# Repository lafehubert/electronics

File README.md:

# electronics
A place for info and code relating to my electronics projects

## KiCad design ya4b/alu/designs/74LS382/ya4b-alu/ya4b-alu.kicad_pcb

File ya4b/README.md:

Here be schematics and PCB designs for YA4B, the 4-bit computer I'm designing.

I use KiCad (https://www.kicad-pcb.org/) for the designs, and an Arduino Mega 2560 to run the test code.

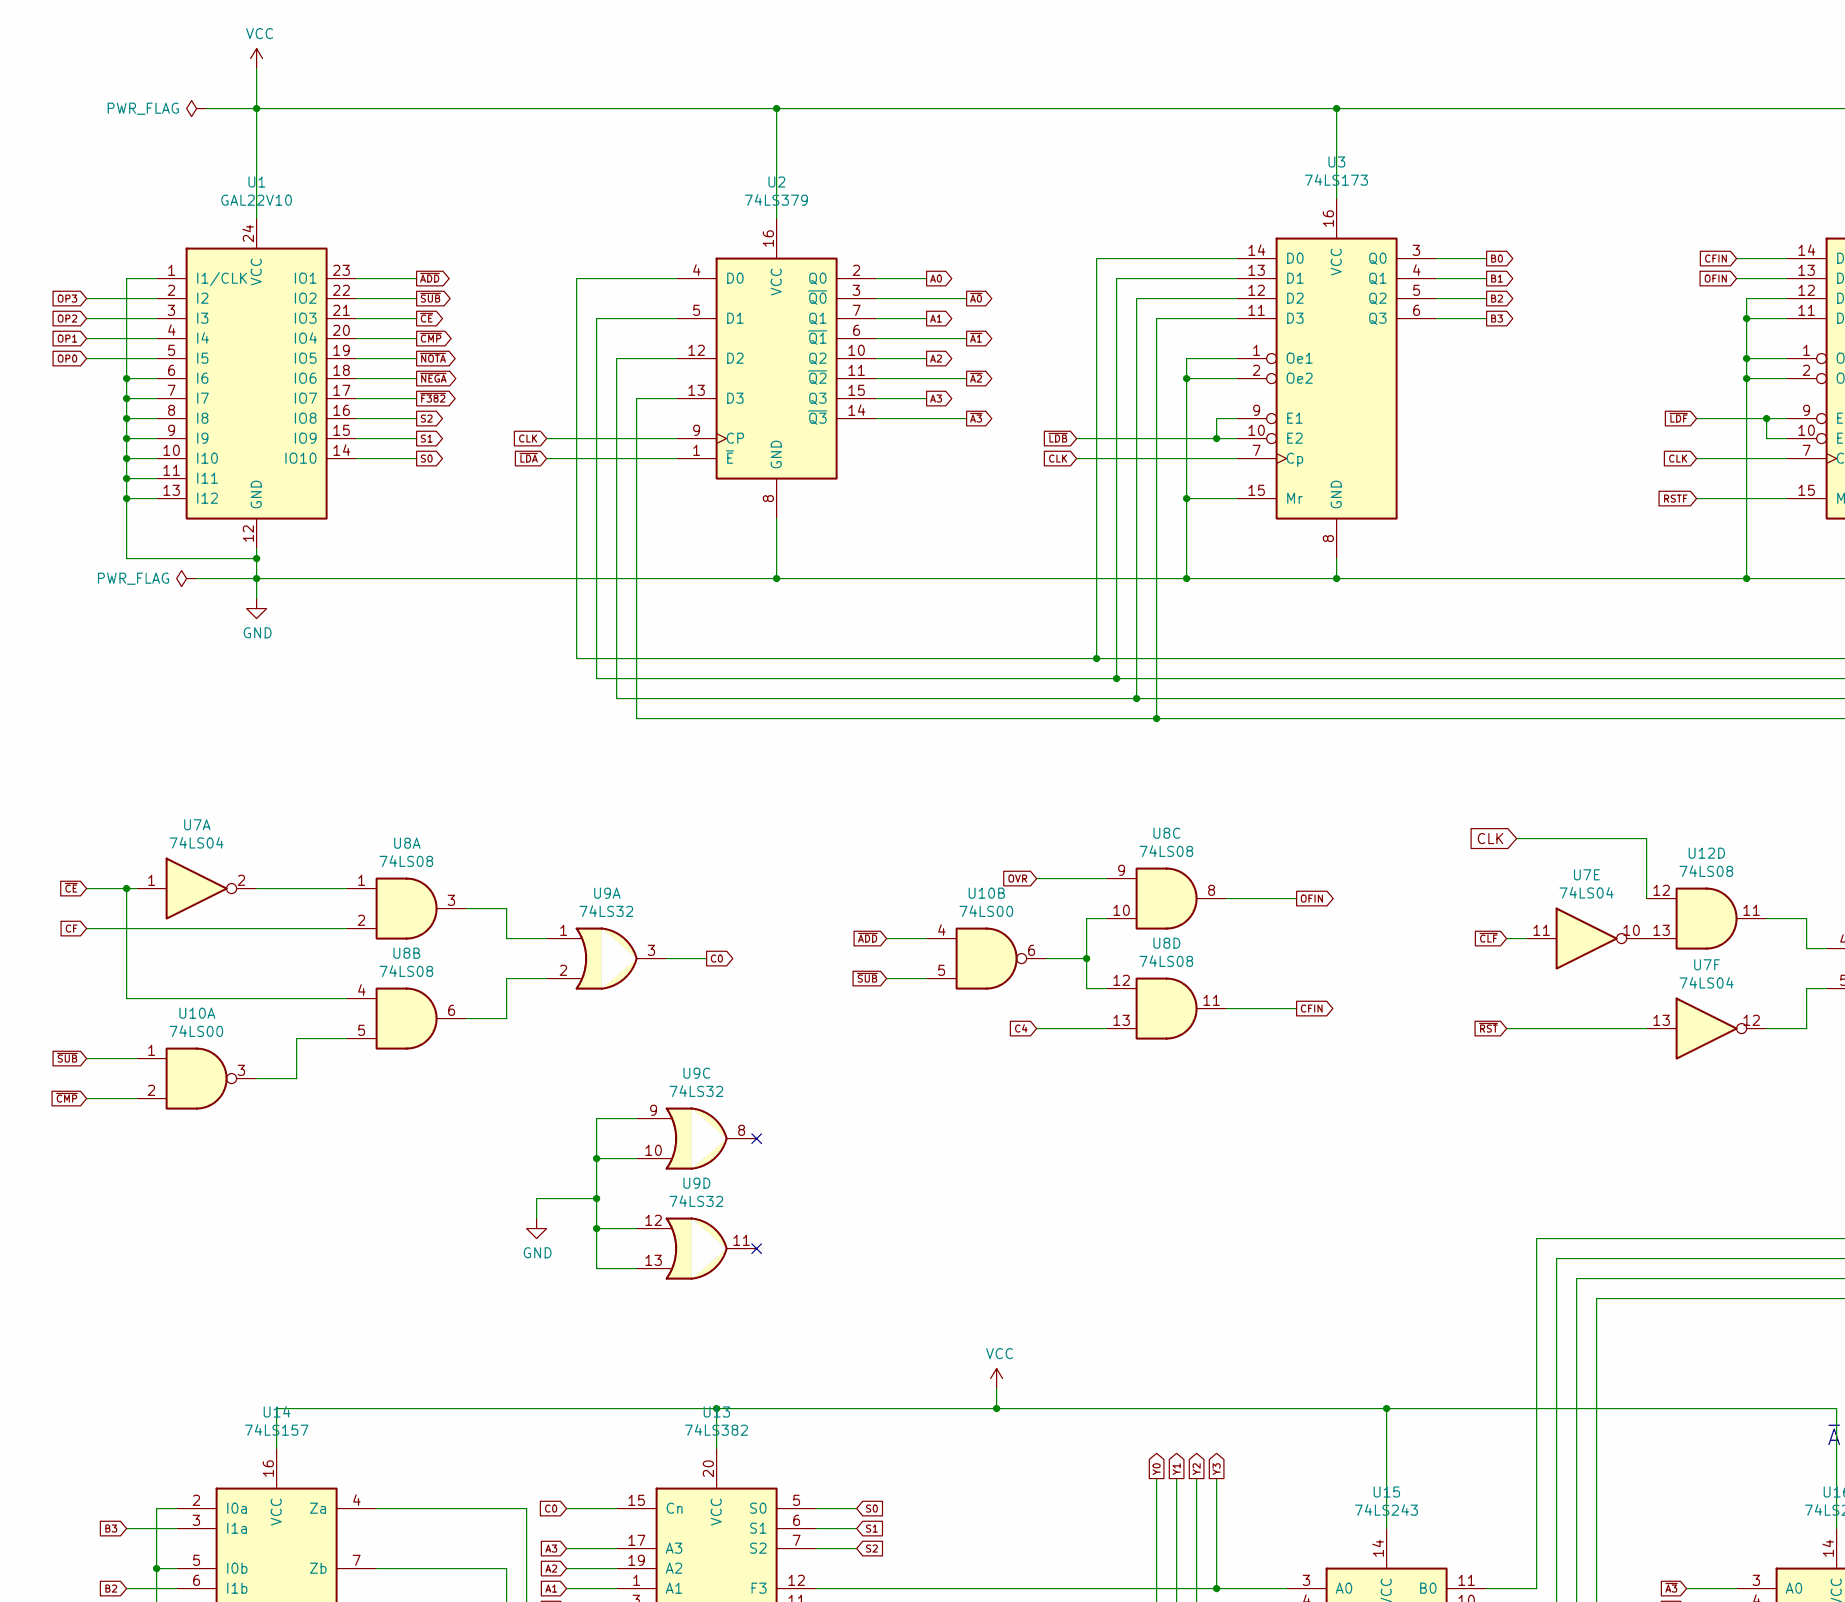
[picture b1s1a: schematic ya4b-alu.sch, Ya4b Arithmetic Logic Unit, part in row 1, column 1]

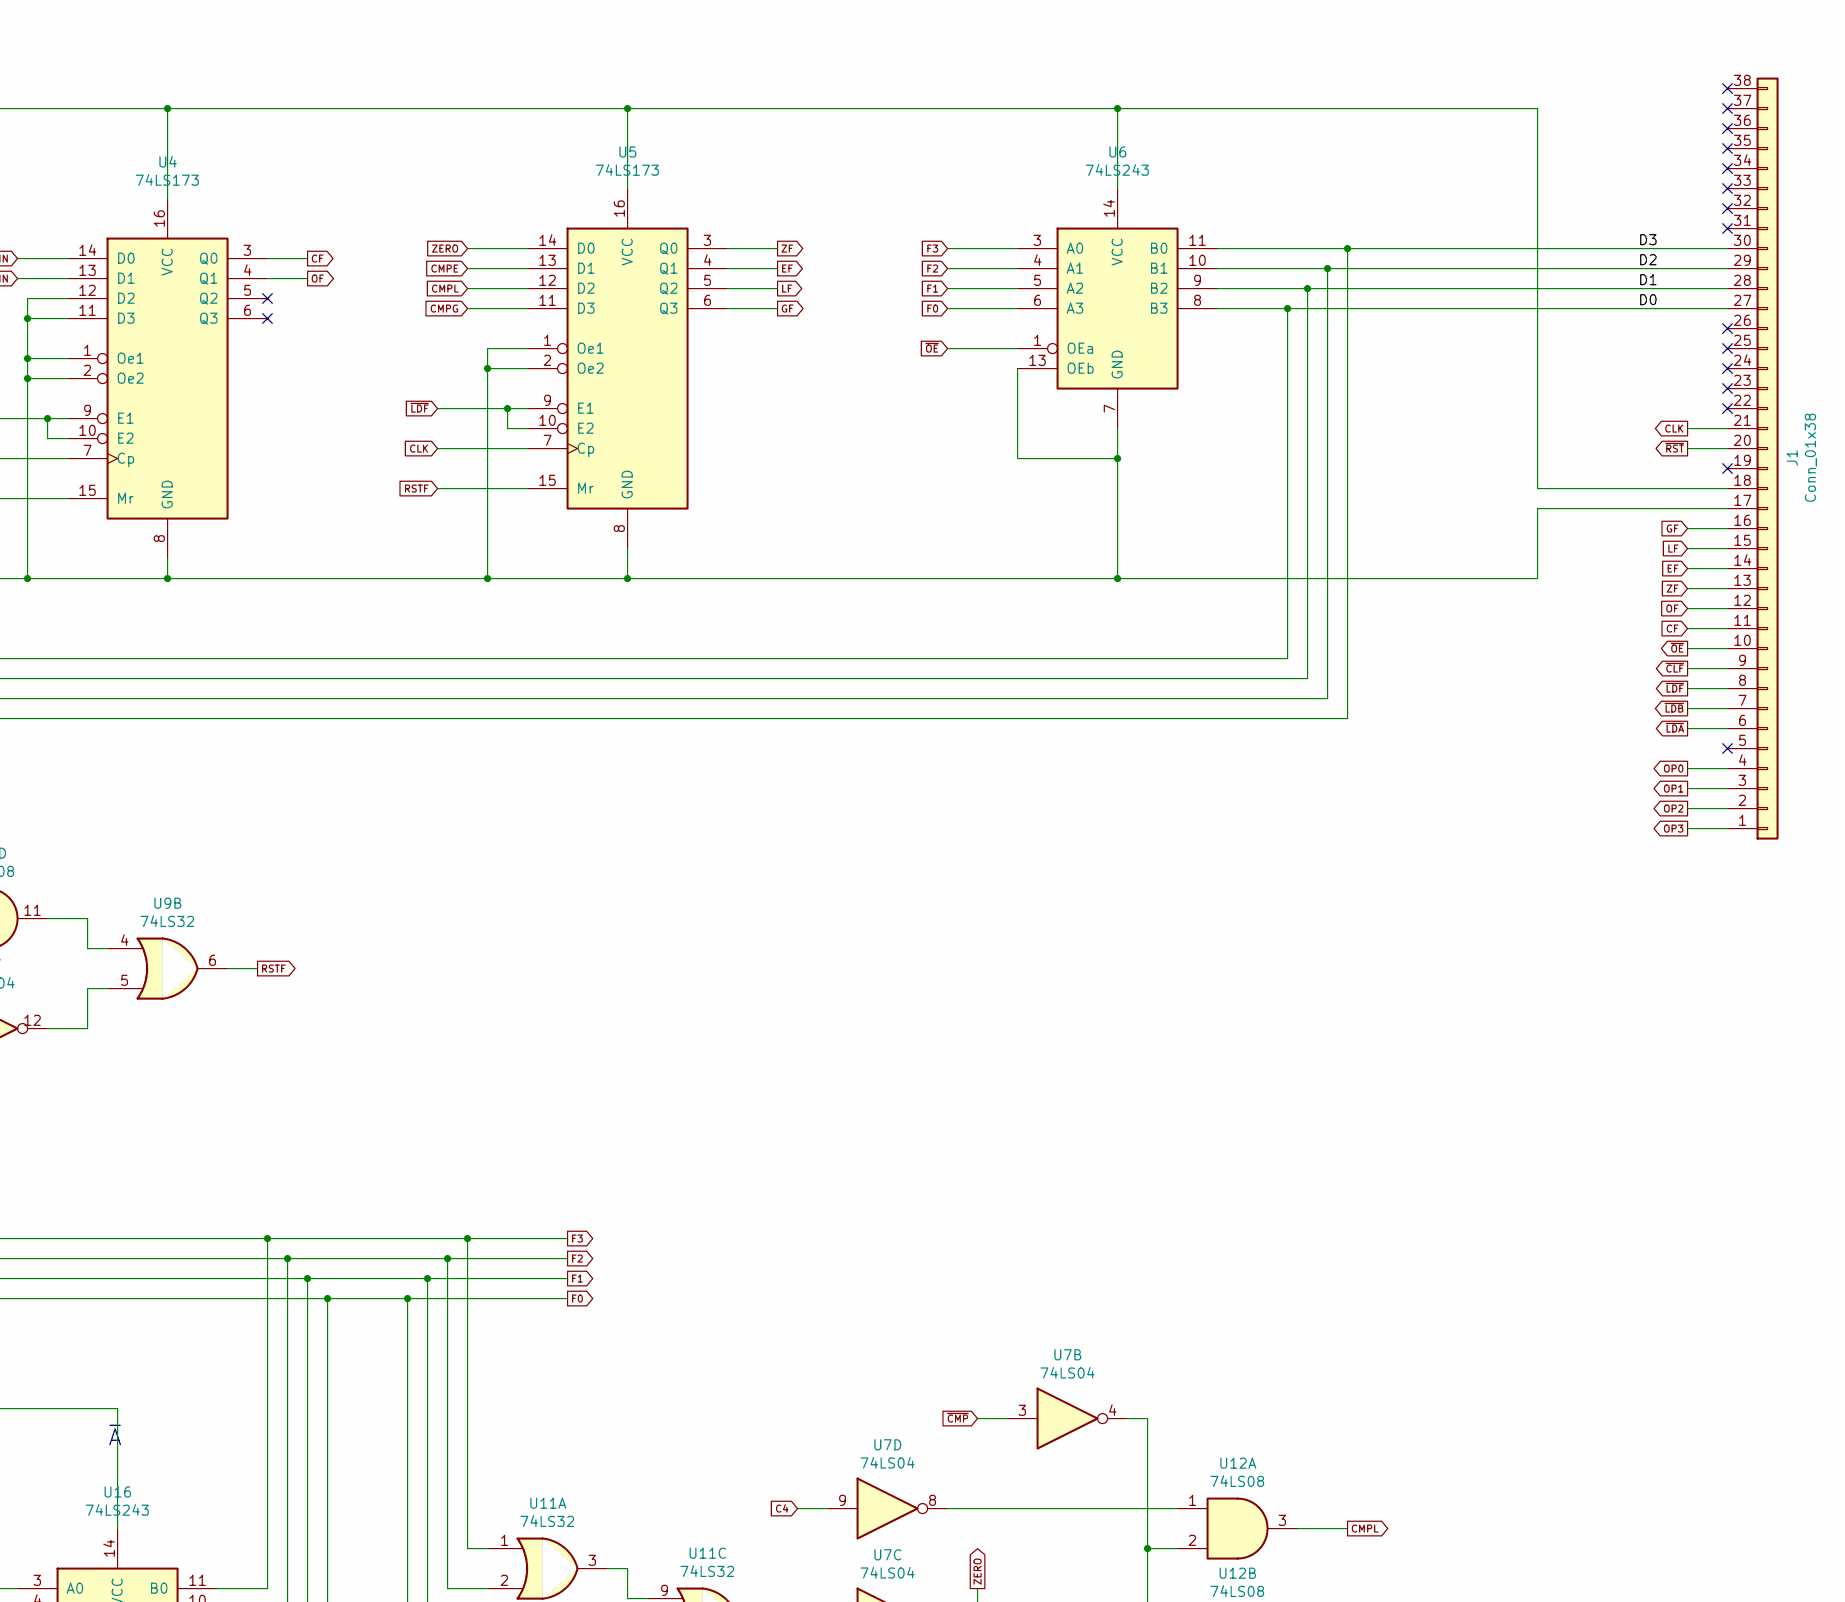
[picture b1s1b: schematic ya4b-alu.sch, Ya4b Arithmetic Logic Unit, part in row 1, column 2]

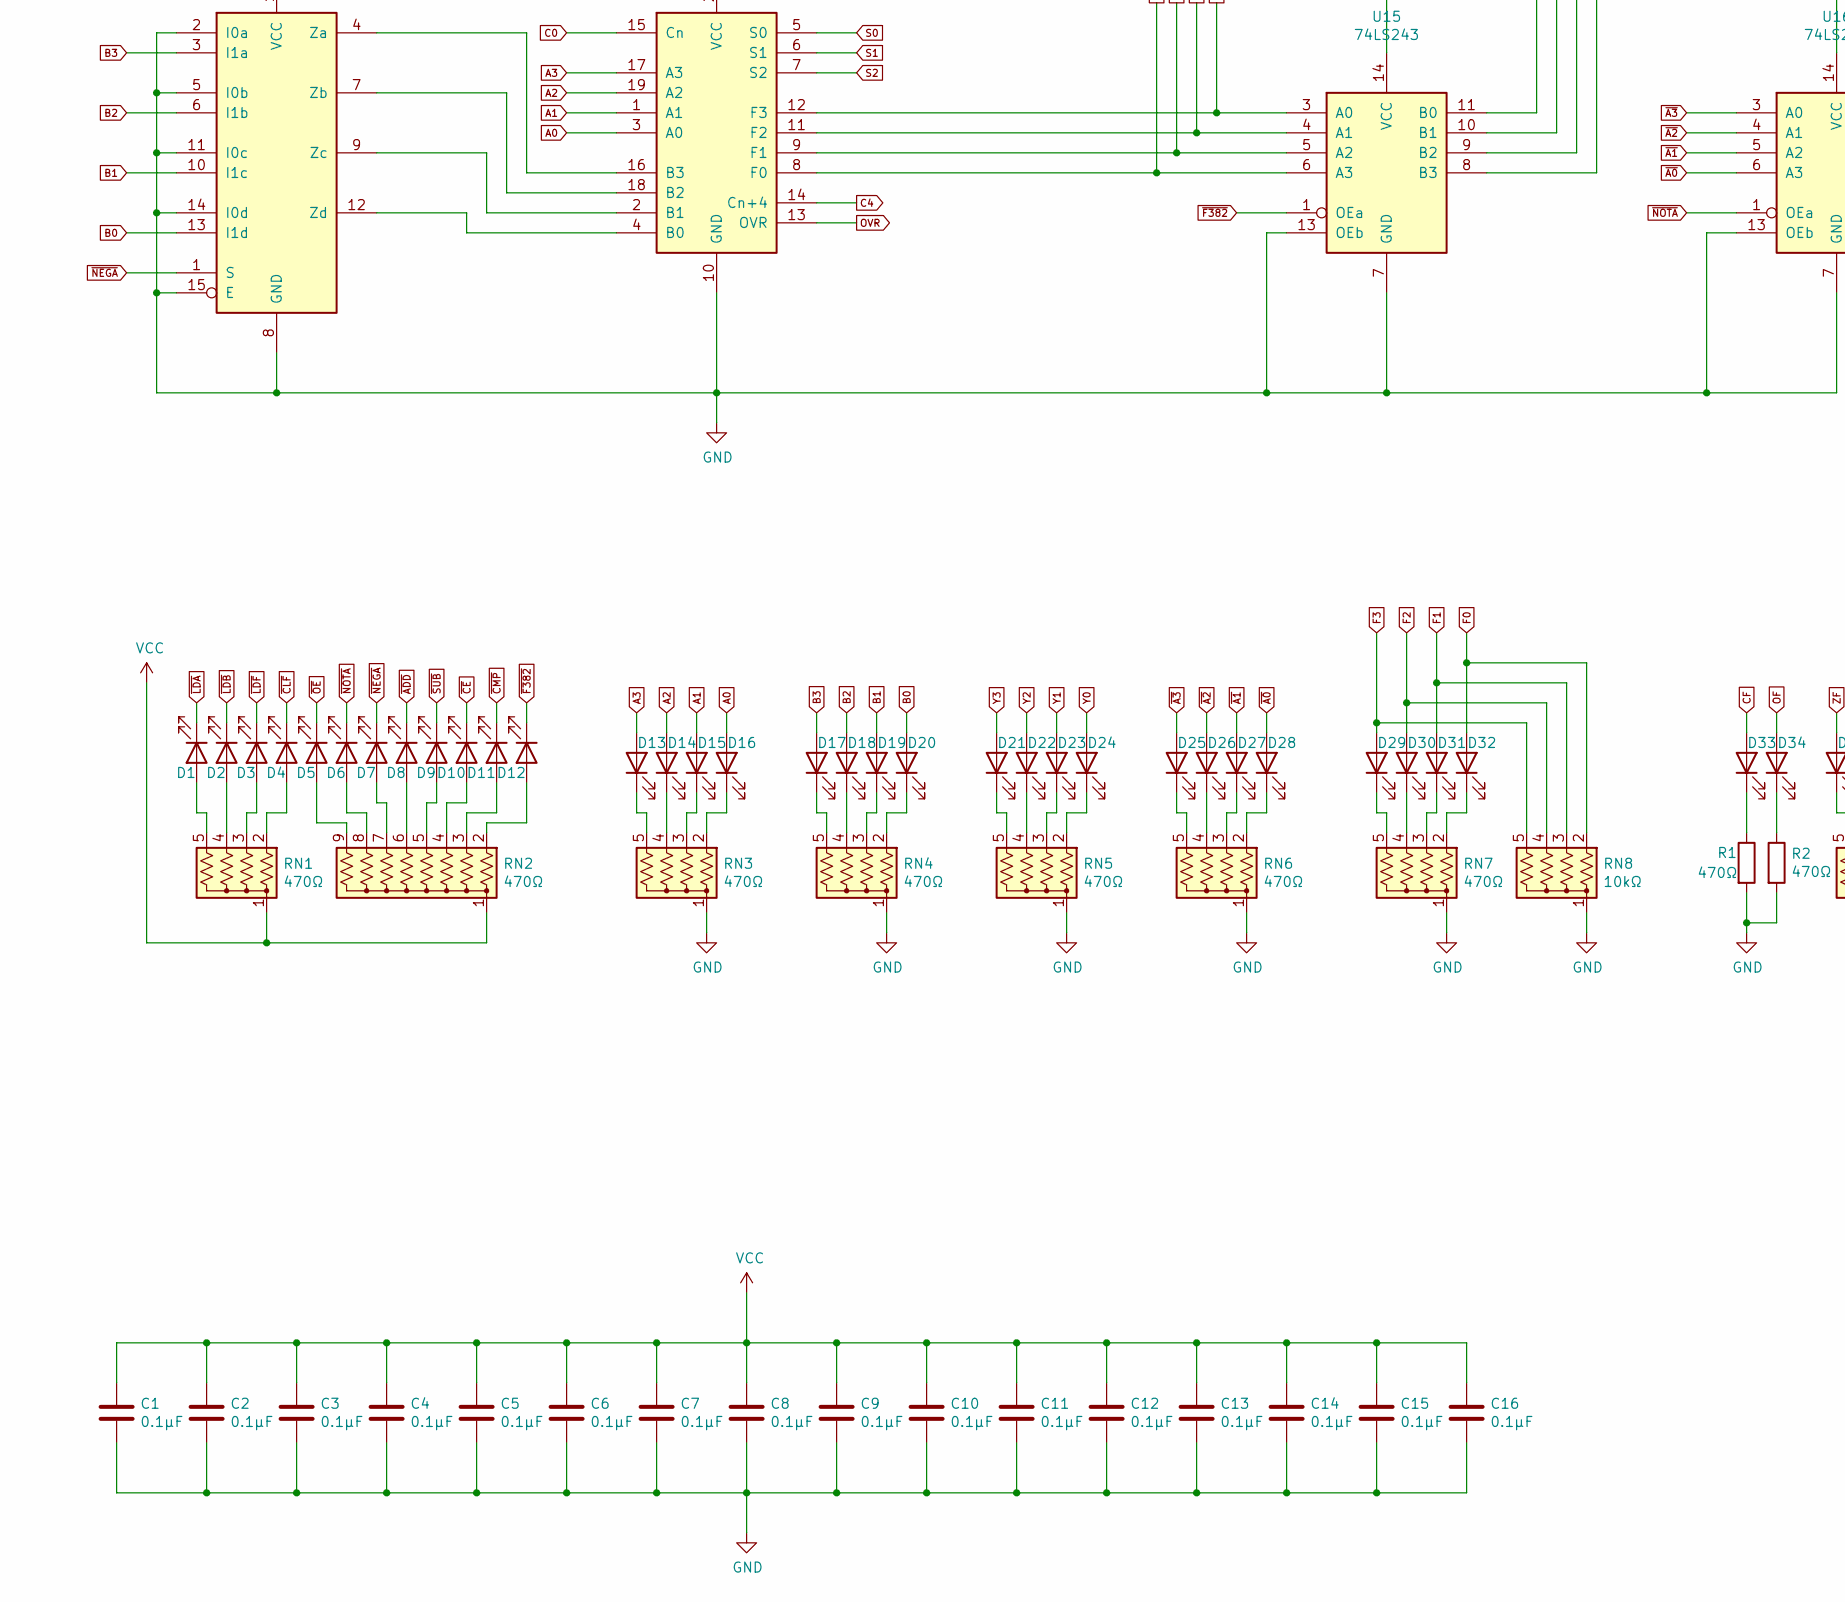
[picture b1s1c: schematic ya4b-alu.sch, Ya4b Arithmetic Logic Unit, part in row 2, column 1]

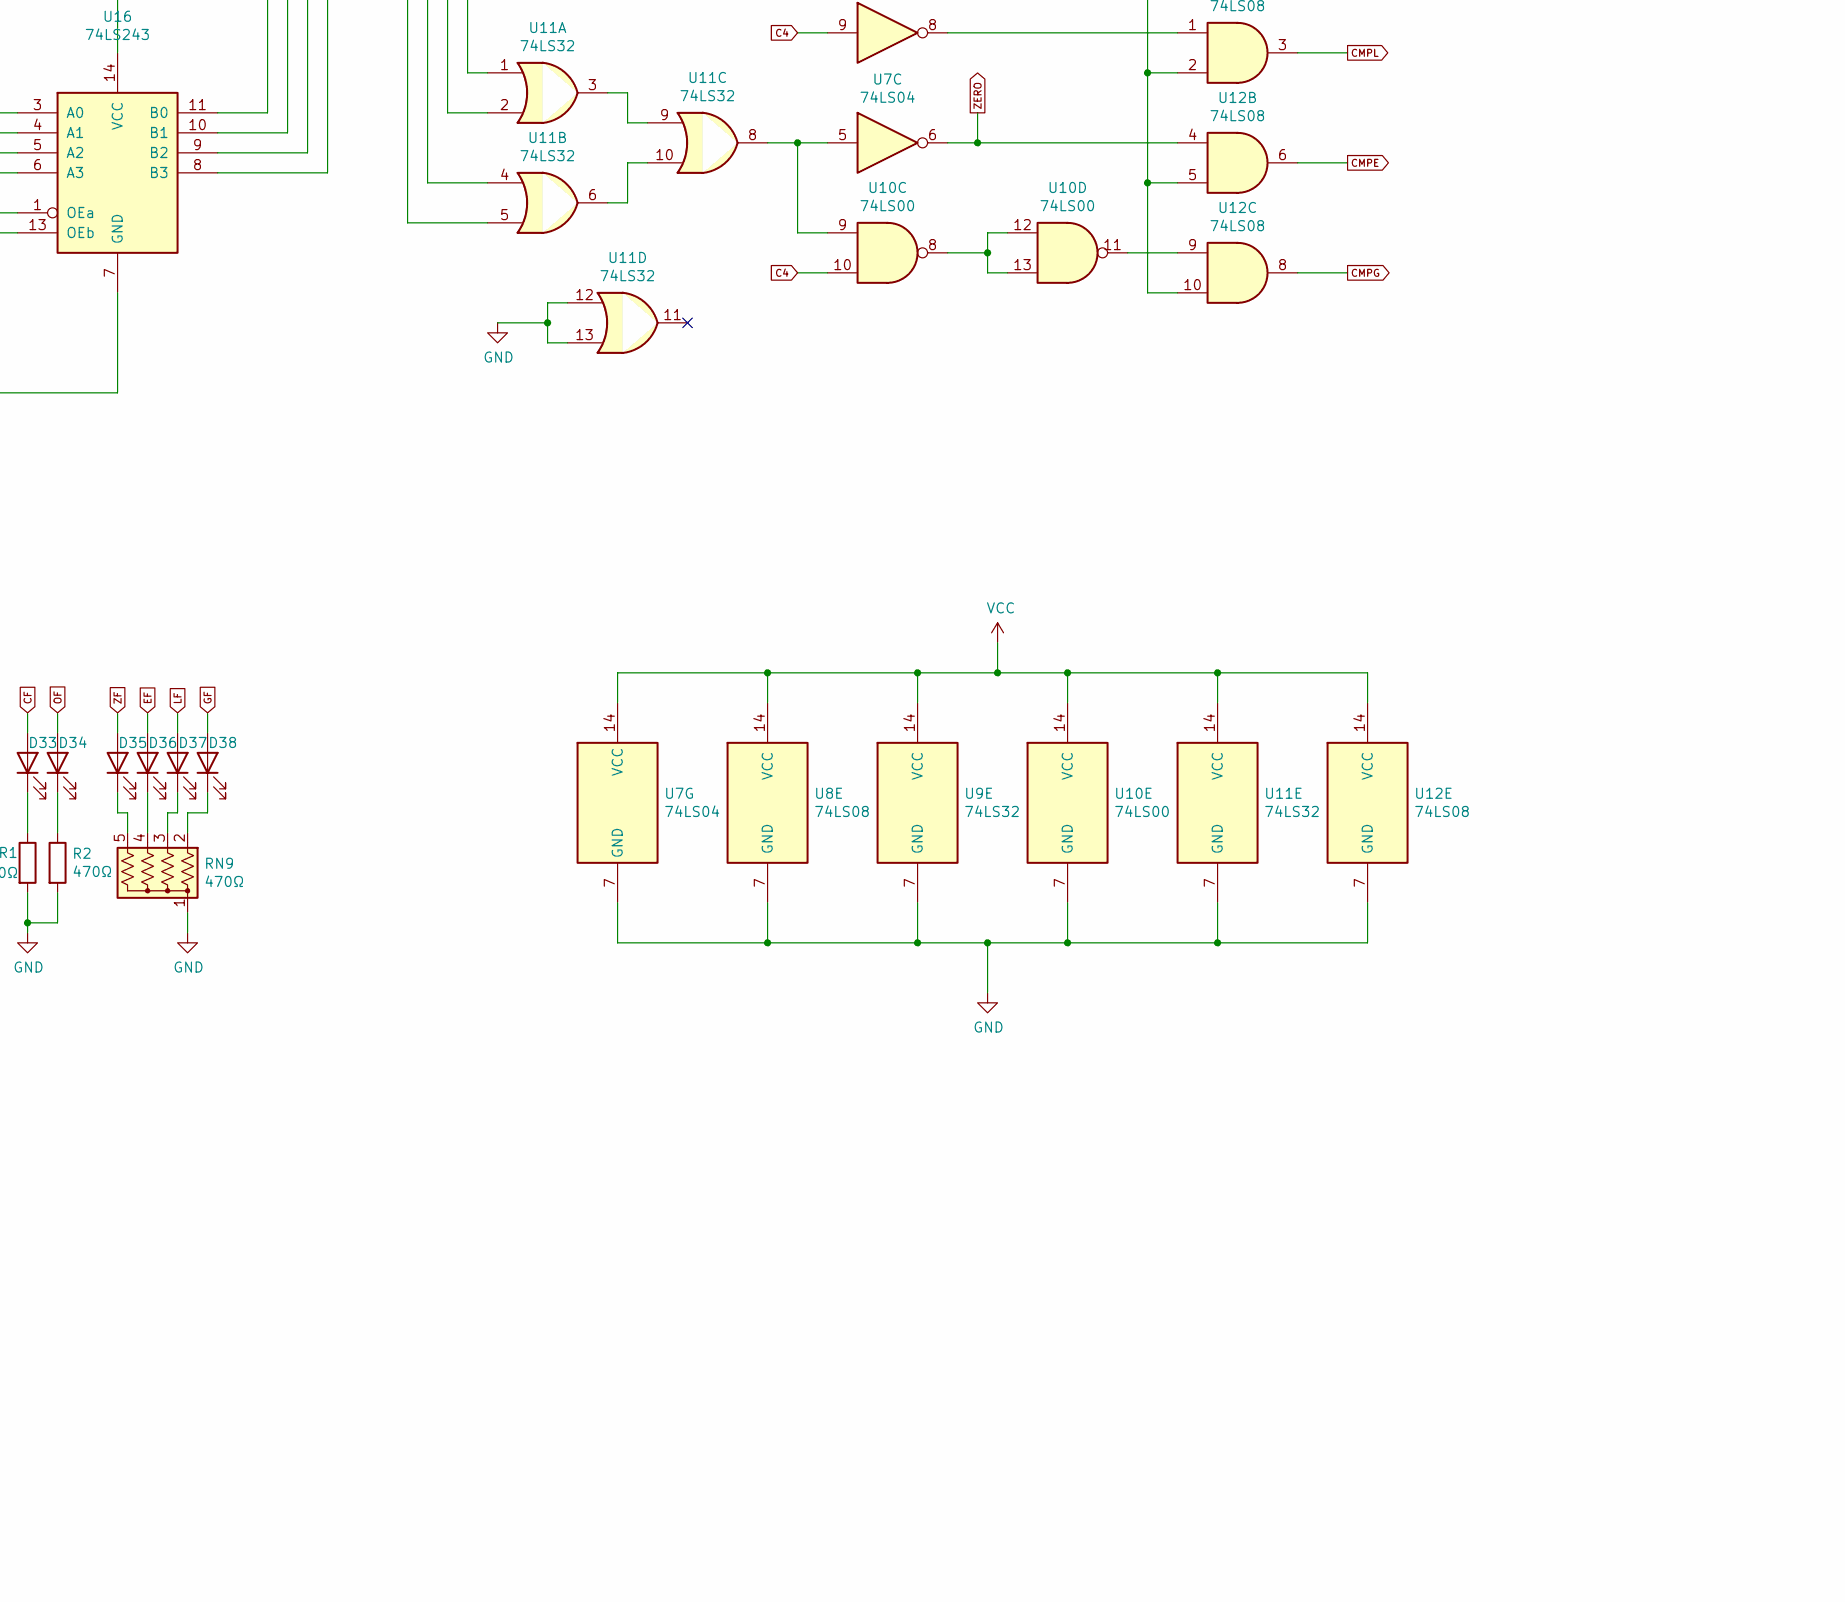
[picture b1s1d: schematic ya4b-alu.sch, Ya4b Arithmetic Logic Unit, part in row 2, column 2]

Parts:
C1, C2, C3, C4, C5, C6, C7, C8, C9, C10, C11, C12, C13, C14, C15, C16: 0.1µF; C_Disc_D3.0mm_W1.6mm_P2.50mm
D1, D2, D3, D4, D5, D6, D7, D8, D9, D10, D11, D12, D13, D14, D15, D16, D17, D18, D19, D20, D21, D22, D23, D24, D25, D26, D27, D28, D29, D30, D31, D32, D33, D34, D35, D36, D37, D38: LED; LED_Rectangular_W5.0mm_H2.0mm
J1: Conn_01x38; PinHeader_1x38_P2.54mm_Vertical
R1, R2: 470Ω; R_Axial_DIN0207_L6.3mm_D2.5mm_P10.16mm_Horizontal
RN1, RN3, RN4, RN5, RN6, RN7, RN9: 470Ω; R_Array_SIP5
RN2: 470Ω; R_Array_SIP9
RN8: 10kΩ; R_Array_SIP5
U1: GAL22V10; DIP-24_W7.62mm_Socket
U2: 74LS379; DIP-16_W7.62mm_Socket
U3, U4, U5: 74LS173; DIP-16_W7.62mm_Socket
U6, U15, U16: 74LS243; DIP-14_W7.62mm_Socket
U7: 74LS04; DIP-14_W7.62mm_Socket
U8, U12: 74LS08; DIP-14_W7.62mm_Socket
U9, U11: 74LS32; DIP-14_W7.62mm_Socket
U10: 74LS00; DIP-14_W7.62mm_Socket
U13: 74LS382; DIP-20_W7.62mm_Socket
U14: 74LS157; DIP-16_W7.62mm_Socket

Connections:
/D0: J1.27, U2.4 (D0), U3.14 (D0), U6.8 (B3)
/D1: J1.28, U2.5 (D1), U3.13 (D1), U6.9 (B2)
/D2: J1.29, U2.12 (D2), U3.12 (D2), U6.10 (B1)
/D3: J1.30, U2.13 (D3), U3.11 (D3), U6.11 (B0)
A0: D16.2 (A), U2.2 (Q0), U13.3 (A0)
A1: D15.2 (A), U2.7 (Q1), U13.1 (A1)
A2: D14.2 (A), U2.10 (Q2), U13.19 (A2)
A3: D13.2 (A), U2.15 (Q3), U13.17 (A3)
B0: D20.2 (A), U3.3 (Q0), U14.13 (I1d)
B1: D19.2 (A), U3.4 (Q1), U14.10 (I1c)
B2: D18.2 (A), U3.5 (Q2), U14.6 (I1b)
B3: D17.2 (A), U3.6 (Q3), U14.3 (I1a)
C0: U9.3, U13.15 (Cn)
C4: U7.9, U8.13, U10.10, U13.14 (Cn+4)
CF: D33.2 (A), J1.11, U4.3 (Q0), U8.2
CFIN: U4.14 (D0), U8.11
CLK: J1.21, U2.9 (CP), U3.7 (Cp), U4.7 (Cp), U5.7 (Cp), U12.12
CMPE: U5.13 (D1), U12.6
CMPG: U5.11 (D3), U12.8
CMPL: U5.12 (D2), U12.3
EF: D36.2 (A), J1.14, U5.4 (Q1)
F0: D32.2 (A), RN8.2 (R1), U6.6 (A3), U11.5, U15.8 (B3), U16.8 (B3)
F1: D31.2 (A), RN8.3 (R2), U6.5 (A2), U11.4, U15.9 (B2), U16.9 (B2)
F2: D30.2 (A), RN8.4 (R3), U6.4 (A1), U11.2, U15.10 (B1), U16.10 (B1)
F3: D29.2 (A), RN8.5 (R4), U6.3 (A0), U11.1, U15.11 (B0), U16.11 (B0)
GF: D38.2 (A), J1.16, U5.6 (Q3)
GND: C1.2, C2.2, C3.2, C4.2, C5.2, C6.2, C7.2, C8.2, C9.2, C10.2, C11.2, C12.2, C13.2, C14.2, C15.2, C16.2, J1.17, R1.2, R2.2, RN3.1 (common), RN4.1 (common), RN5.1 (common), RN6.1 (common), RN7.1 (common), RN8.1 (common), RN9.1 (common), U1.1 (I1/CLK), U1.6 (I6), U1.7 (I7), U1.8 (I8), U1.9 (I9), U1.10 (I10), U1.11 (I11), U1.12 (GND), U1.13 (I12), U2.8 (GND), U3.1 (Oe1), U3.2 (Oe2), U3.8 (GND), U3.15 (Mr), U4.1 (Oe1), U4.2 (Oe2), U4.8 (GND), U4.11 (D3), U4.12 (D2), U5.1 (Oe1), U5.2 (Oe2), U5.8 (GND), U6.7 (GND), U6.13 (OEb), U7.7 (GND), U8.7 (GND), U9.7 (GND), U9.9, U9.10, U9.12, U9.13, U10.7 (GND), U11.7 (GND), U11.12, U11.13, U12.7 (GND), U13.10 (GND), U14.2 (I0a), U14.5 (I0b), U14.8 (GND), U14.11 (I0c), U14.14 (I0d), U14.15 (E), U15.7 (GND), U15.13 (OEb), U16.7 (GND), U16.13 (OEb)
LF: D37.2 (A), J1.15, U5.5 (Q2)
unnamed: D1.2 (A), RN1.5 (R4)
unnamed: D2.2 (A), RN1.4 (R3)
unnamed: D3.2 (A), RN1.3 (R2)
unnamed: D4.2 (A), RN1.2 (R1)
unnamed: D5.2 (A), RN2.9 (R8)
unnamed: D6.2 (A), RN2.8 (R7)
unnamed: D7.2 (A), RN2.7 (R6)
unnamed: D8.2 (A), RN2.6 (R5)
unnamed: D9.2 (A), RN2.5 (R4)
unnamed: D10.2 (A), RN2.4 (R3)
unnamed: D11.2 (A), RN2.3 (R2)
unnamed: D12.2 (A), RN2.2 (R1)
unnamed: D13.1 (K), RN3.5 (R4)
unnamed: D14.1 (K), RN3.4 (R3)
unnamed: D15.1 (K), RN3.3 (R2)
unnamed: D16.1 (K), RN3.2 (R1)
unnamed: D17.1 (K), RN4.5 (R4)
unnamed: D18.1 (K), RN4.4 (R3)
unnamed: D19.1 (K), RN4.3 (R2)
unnamed: D20.1 (K), RN4.2 (R1)
unnamed: D21.1 (K), RN5.5 (R4)
unnamed: D22.1 (K), RN5.4 (R3)
unnamed: D23.1 (K), RN5.3 (R2)
unnamed: D24.1 (K), RN5.2 (R1)
unnamed: D25.1 (K), RN6.5 (R4)
unnamed: D26.1 (K), RN6.4 (R3)
unnamed: D27.1 (K), RN6.3 (R2)
unnamed: D28.1 (K), RN6.2 (R1)
unnamed: D29.1 (K), RN7.5 (R4)
unnamed: D30.1 (K), RN7.4 (R3)
unnamed: D31.1 (K), RN7.3 (R2)
unnamed: D32.1 (K), RN7.2 (R1)
unnamed: D33.1 (K), R1.1
unnamed: D34.1 (K), R2.1
unnamed: D35.1 (K), RN9.5 (R4)
unnamed: D36.1 (K), RN9.4 (R3)
unnamed: D37.1 (K), RN9.3 (R2)
unnamed: D38.1 (K), RN9.2 (R1)
unnamed: U7.2, U8.1
unnamed: U7.12, U9.5
unnamed: U8.3, U9.1
unnamed: U8.6, U9.2
unnamed: U8.5, U10.3
unnamed: U8.10, U8.12, U10.6
unnamed: U7.5, U10.9, U11.8
unnamed: U10.11, U12.9
unnamed: U10.8, U10.12, U10.13
unnamed: U11.3, U11.9
unnamed: U11.6, U11.10
unnamed: U7.8, U12.1
unnamed: U7.4, U12.2, U12.5, U12.10
unnamed: U9.4, U12.11
unnamed: U7.10, U12.13
unnamed: U13.2 (B1), U14.9 (Zc)
unnamed: U13.4 (B0), U14.12 (Zd)
unnamed: U13.16 (B3), U14.4 (Za)
unnamed: U13.18 (B2), U14.7 (Zb)
OF: D34.2 (A), J1.12, U4.4 (Q1)
OFIN: U4.13 (D1), U8.8
OP0: J1.4, U1.5 (I5)
OP1: J1.3, U1.4 (I4)
OP2: J1.2, U1.3 (I3)
OP3: J1.1, U1.2 (I2)
OVR: U8.9, U13.13 (OVR)
RSTF: U4.15 (Mr), U5.15 (Mr), U9.6
S0: U1.14 (IO10), U13.5 (S0)
S1: U1.15 (IO9), U13.6 (S1)
S2: U1.16 (IO8), U13.7 (S2)
VCC: C1.1, C2.1, C3.1, C4.1, C5.1, C6.1, C7.1, C8.1, C9.1, C10.1, C11.1, C12.1, C13.1, C14.1, C15.1, C16.1, J1.18, RN1.1 (common), RN2.1 (common), U1.24 (VCC), U2.16 (VCC), U3.16 (VCC), U4.16 (VCC), U5.16 (VCC), U6.14 (VCC), U7.14 (VCC), U8.14 (VCC), U9.14 (VCC), U10.14 (VCC), U11.14 (VCC), U12.14 (VCC), U13.20 (VCC), U14.16 (VCC), U15.14 (VCC), U16.14 (VCC)
Y0: D24.2 (A), U13.8 (F0), U15.6 (A3)
Y1: D23.2 (A), U13.9 (F1), U15.5 (A2)
Y2: D22.2 (A), U13.11 (F2), U15.4 (A1)
Y3: D21.2 (A), U13.12 (F3), U15.3 (A0)
ZERO: U5.14 (D0), U7.6, U12.4
ZF: D35.2 (A), J1.13, U5.3 (Q0)
~A0: D28.2 (A), U2.3 (~Q0), U16.6 (A3)
~A1: D27.2 (A), U2.6 (~Q1), U16.5 (A2)
~A2: D26.2 (A), U2.11 (~Q2), U16.4 (A1)
~A3: D25.2 (A), U2.14 (~Q3), U16.3 (A0)
~ADD: D8.1 (K), U1.23 (IO1), U10.4
~CE: D10.1 (K), U1.21 (IO3), U7.1, U8.4
~CLF: D4.1 (K), J1.9, U7.11
~CMP: D11.1 (K), U1.20 (IO4), U7.3, U10.2
~F382: D12.1 (K), U1.17 (IO7), U15.1 (OEa)
~LDA: D1.1 (K), J1.6, U2.1 (~E)
~LDB: D2.1 (K), J1.7, U3.9 (E1), U3.10 (E2)
~LDF: D3.1 (K), J1.8, U4.9 (E1), U4.10 (E2), U5.9 (E1), U5.10 (E2)
~NEGA: D7.1 (K), U1.18 (IO6), U14.1 (S)
~NOTA: D6.1 (K), U1.19 (IO5), U16.1 (OEa)
~OE: D5.1 (K), J1.10, U6.1 (OEa)
~RST: J1.20, U7.13
~SUB: D9.1 (K), U1.22 (IO2), U10.1, U10.5

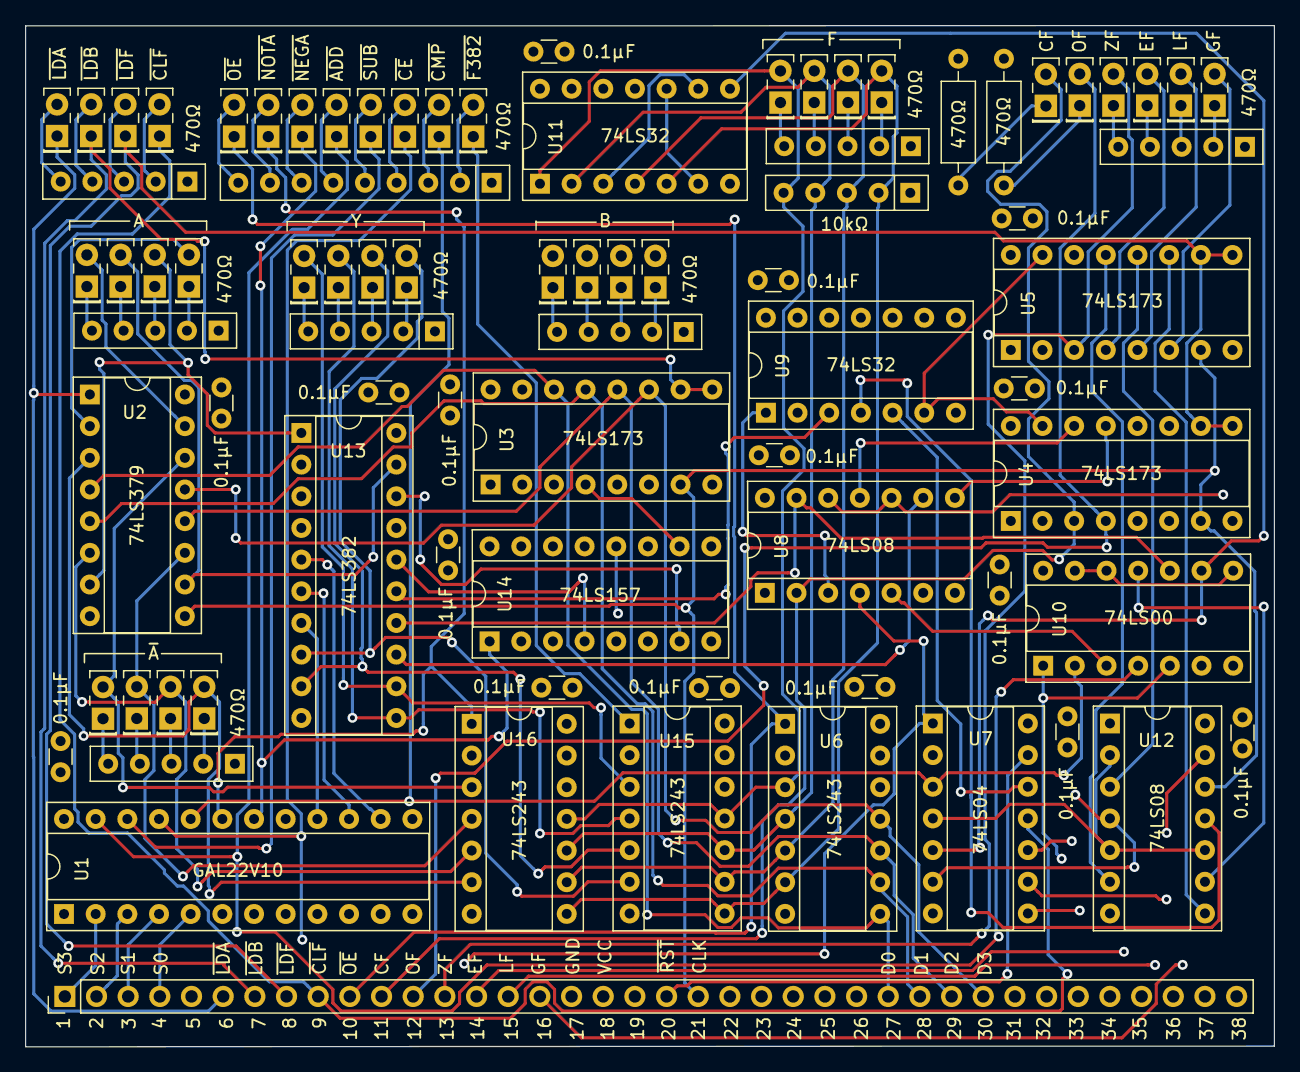
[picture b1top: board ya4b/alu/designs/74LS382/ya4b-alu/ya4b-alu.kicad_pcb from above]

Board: 4 copper layers, 100.2 x 81.9 mm, 82 parts (0 on the bottom side), 120 nets.

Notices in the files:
ya4b/address-register/address-register-bank/address-register-bank.kicad_pcb:
© 2020 Gregory Martin
ya4b/slow-clock/slow-clock.kicad_pcb:
© 2019 Gregory Martin
